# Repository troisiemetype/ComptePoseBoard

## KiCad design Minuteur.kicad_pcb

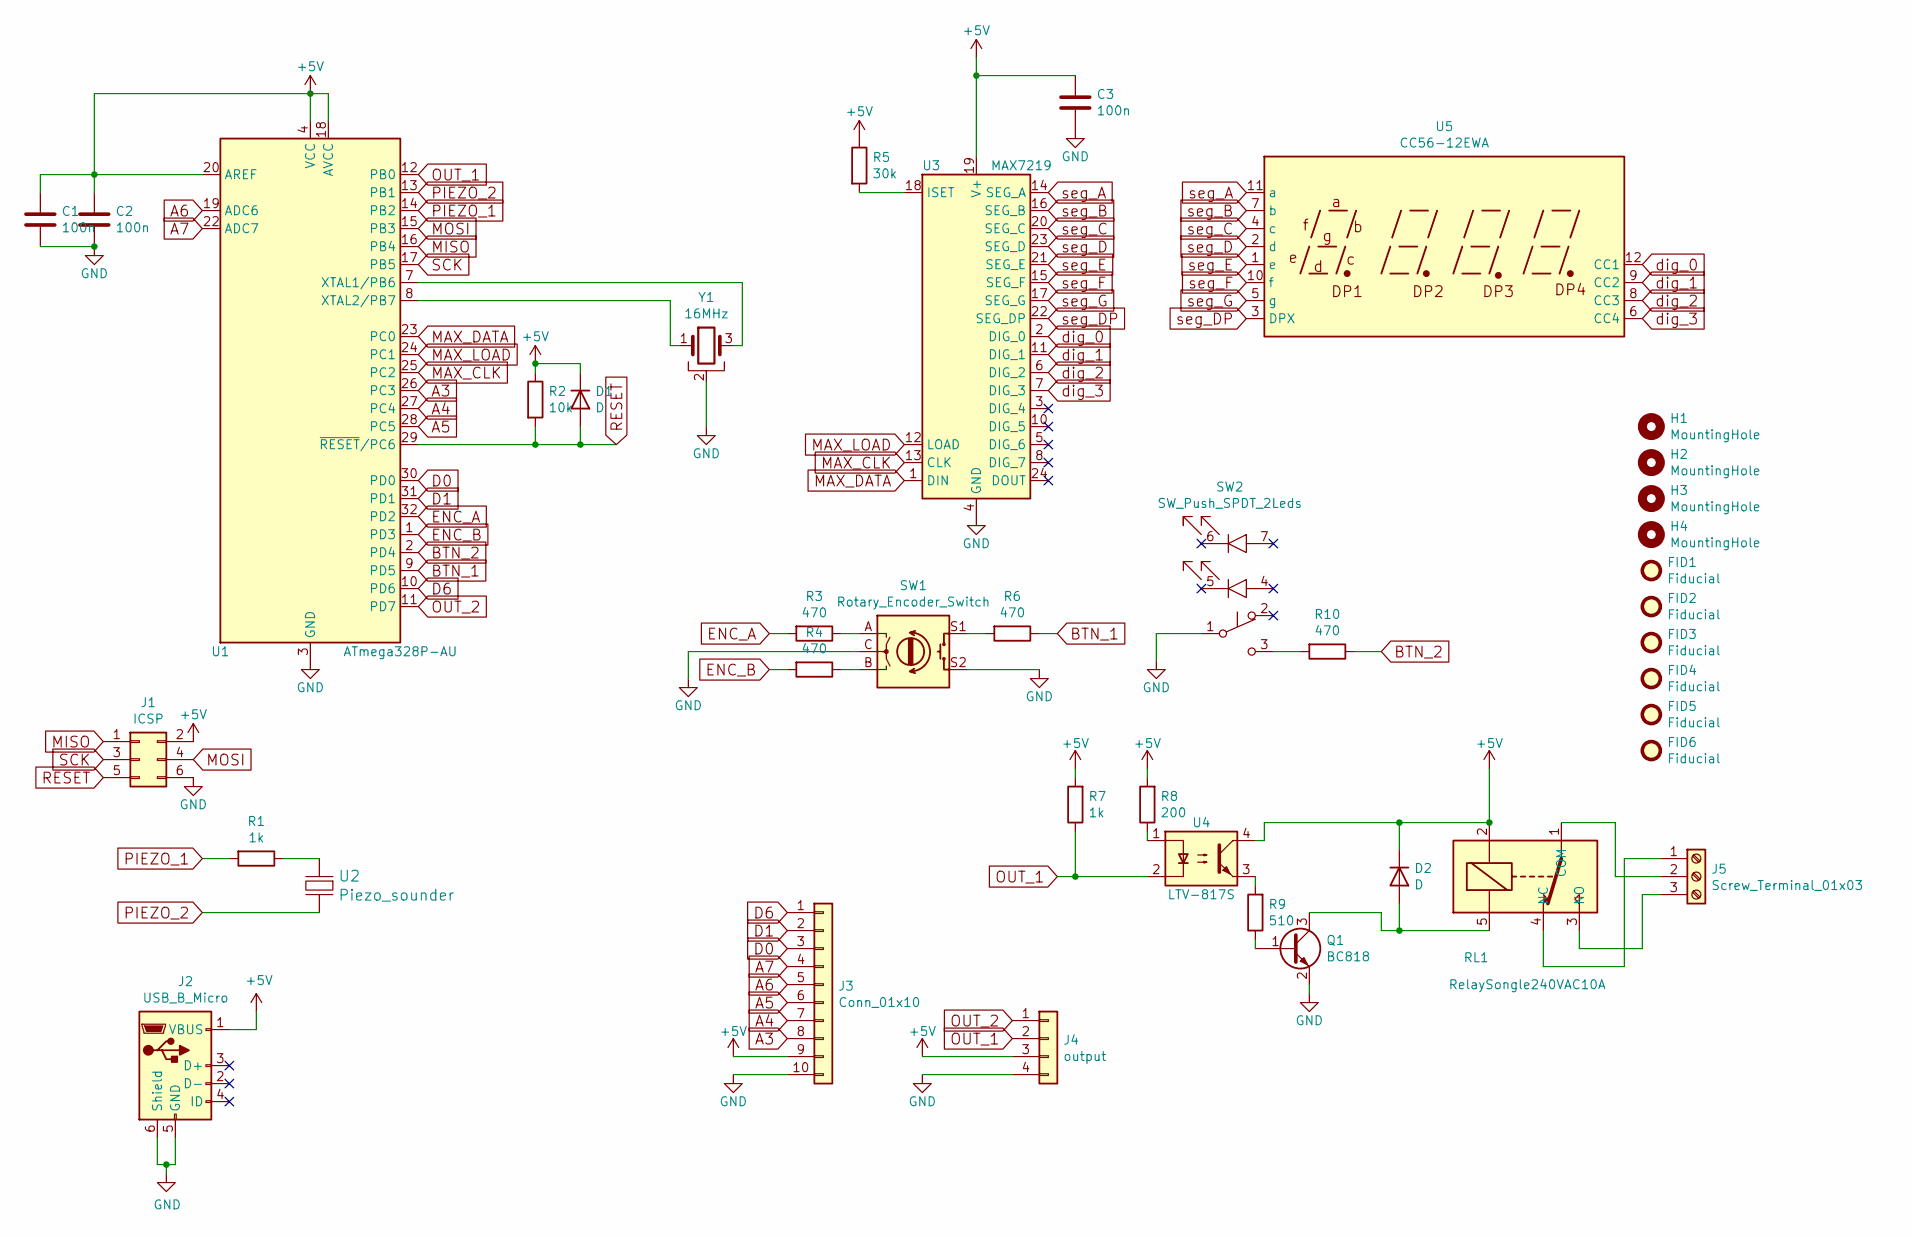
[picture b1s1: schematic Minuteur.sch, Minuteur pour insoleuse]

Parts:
C1, C2, C3: 100n; C_0805_2012Metric
D1, D2: D; D_SOD-123
FID1, FID2, FID3, FID4, FID5, FID6: Fiducial; Fiducial_0.75mm_Mask1.5mm
H1, H2, H3, H4: MountingHole; MountingHole_3.2mm_M3
J1: ICSP; PinHeader_2x03_P2.54mm_Vertical
J2: USB_B_Micro; USB_Micro-B_Amphenol_10118194_Horizontal
J3: Conn_01x10; PinHeader_1x10_P2.54mm_Vertical
J4: output; PinHeader_1x04_P2.54mm_Vertical
J5: Screw_Terminal_01x03; PhoenixContact_MSTBVA_2,5_3-G-5,08_1x03_P5.08mm_Vertical
Q1: BC818; SOT-23
R1, R7: 1k; R_0805_2012Metric
R2: 10k; R_0805_2012Metric
R3, R4, R6, R10: 470; R_0805_2012Metric
R5: 30k; R_0805_2012Metric
R8: 200; R_0805_2012Metric
R9: 510; R_0805_2012Metric
RL1: RelaySongle240VAC10A; Relay_SPDT_SANYOU_SRD_Series_Form_C
SW1: Rotary_Encoder_Switch; RotaryEncoder_Alps_EC12E-Switch_Vertical_H20mm_CircularMoun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
SW2: SW_Push_SPDT_2Leds; SP86-THT-PushButton
U1: ATmega328P-AU; TQFP-32_7x7mm_P0.8mm
U2: Piezo_sounder; Murata_PKMCS0909_xxxxx
U3: MAX7219; SOIC-24W_7.5x15.4mm_P1.27mm
U4: LTV-817S; SMDIP-4_W9.53mm
U5: CC56-12EWA; CA56-12EWA
Y1: 16MHz; Resonator_SMD_muRata_CSTxExxV-3Pin_3.0x1.1mm

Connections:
+5V: C1.1, C2.1, C3.1, D1.1 (K), D2.1 (K), J1.2, J2.1 (VBUS), J3.9, J4.3, R2.1, R5.1, R7.2, R8.2, RL1.2, U1.4 (VCC), U1.6 (VCC), U1.18 (AVCC), U1.20 (AREF), U3.19 (V+), U4.4; also elsewhere on the board
A3: J3.8, U1.26 (PC3); also elsewhere on the board
A4: J3.7, U1.27 (PC4); also elsewhere on the board
A5: J3.6, U1.28 (PC5); also elsewhere on the board
A6: J3.5, U1.19 (ADC6); also elsewhere on the board
A7: J3.4, U1.22 (ADC7); also elsewhere on the board
BTN_1: R6.1, U1.9 (PD5)
BTN_2: R10.1, U1.2 (PD4)
D0: J3.3, U1.30 (PD0); also elsewhere on the board
D1: J3.2, U1.31 (PD1); also elsewhere on the board
D6: J3.1, U1.10 (PD6); also elsewhere on the board
ENC_A: R3.2, U1.32 (PD2)
ENC_B: R4.2, U1.1 (PD3)
GND: C1.2, C2.2, C3.2, J1.6, J2.5 (GND), J2.6 (Shield), J3.10, J4.4, Q1.2 (E), SW1.C, SW1.S2, SW2.1 (B), U1.3 (GND), U1.5 (GND), U1.21 (GND), U3.4 (GND), U3.9 (GND), Y1.2; also elsewhere on the board
MAX_CLK: U1.25 (PC2), U3.13 (CLK)
MAX_DATA: U1.23 (PC0), U3.1 (DIN)
MAX_LOAD: U1.24 (PC1), U3.12 (LOAD)
MISO: J1.1, U1.16 (PB4); also elsewhere on the board
MOSI: J1.4, U1.15 (PB3); also elsewhere on the board
unnamed: D2.2 (A), Q1.3 (C), RL1.5
unnamed: J5.1, RL1.4 (NC)
unnamed: J5.2, RL1.1 (COM)
unnamed: J5.3, RL1.3 (NO)
unnamed: Q1.1 (B), R9.1
unnamed: R1.1, U2.1
unnamed: R3.1, SW1.A
unnamed: R4.1, SW1.B
unnamed: R5.2, U3.18 (ISET)
unnamed: R6.2, SW1.S1
unnamed: R8.1, U4.1
unnamed: R9.2, U4.3
unnamed: R10.2, SW2.3 (C)
unnamed: U1.7 (XTAL1/PB6), Y1.3
unnamed: U1.8 (XTAL2/PB7), Y1.1
OUT_1: J4.2, R7.1, U1.12 (PB0), U4.2; also elsewhere on the board
OUT_2: J4.1, U1.11 (PD7); also elsewhere on the board
PIEZO_1: R1.2, U1.14 (PB2)
PIEZO_2: U1.13 (PB1), U2.2
RESET: D1.2 (A), J1.5, R2.2, U1.29 (~RESET~/PC6); also elsewhere on the board
SCK: J1.3, U1.17 (PB5); also elsewhere on the board
dig_0: U3.2 (DIG_0), U5.12 (CC1)
dig_1: U3.11 (DIG_1), U5.9 (CC2)
dig_2: U3.6 (DIG_2), U5.8 (CC3)
dig_3: U3.7 (DIG_3), U5.6 (CC4)
seg_A: U3.14 (SEG_A), U5.11 (a)
seg_B: U3.16 (SEG_B), U5.7 (b)
seg_C: U3.20 (SEG_C), U5.4 (c)
seg_D: U3.23 (SEG_D), U5.2 (d)
seg_DP: U3.22 (SEG_DP), U5.3 (DPX)
seg_E: U3.21 (SEG_E), U5.1 (e)
seg_F: U3.15 (SEG_F), U5.10 (f)
seg_G: U3.17 (SEG_G), U5.5 (g)

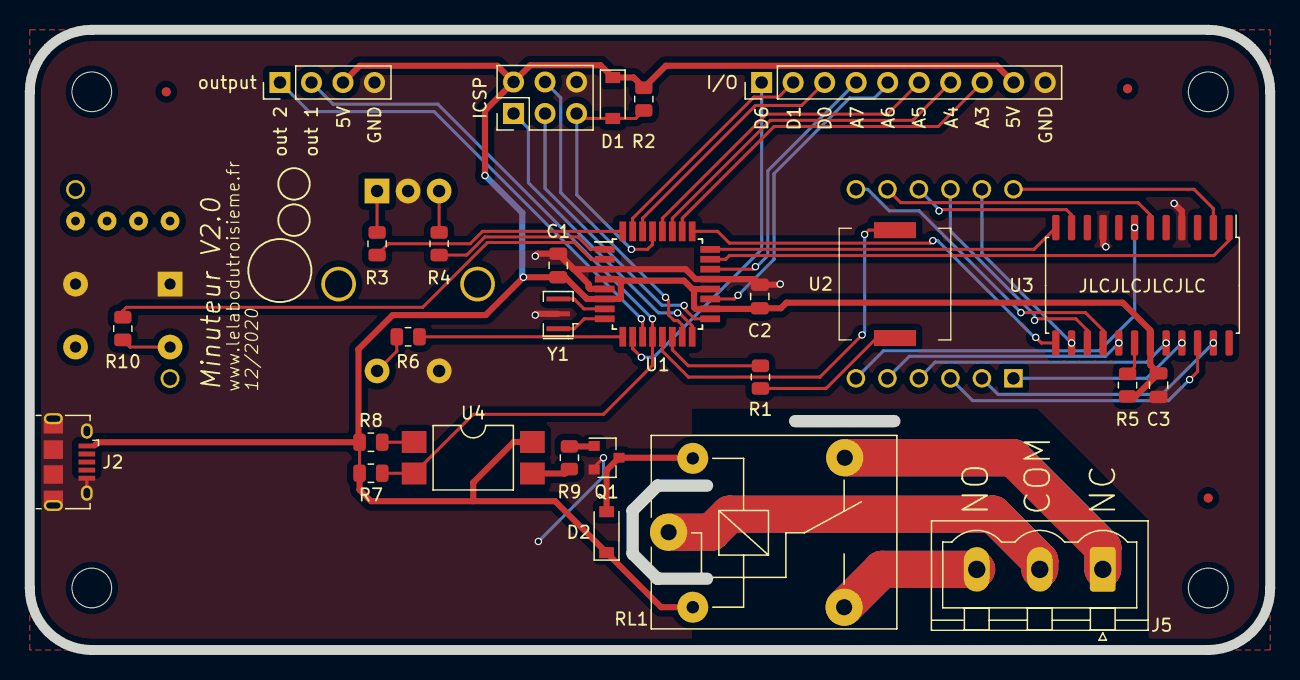
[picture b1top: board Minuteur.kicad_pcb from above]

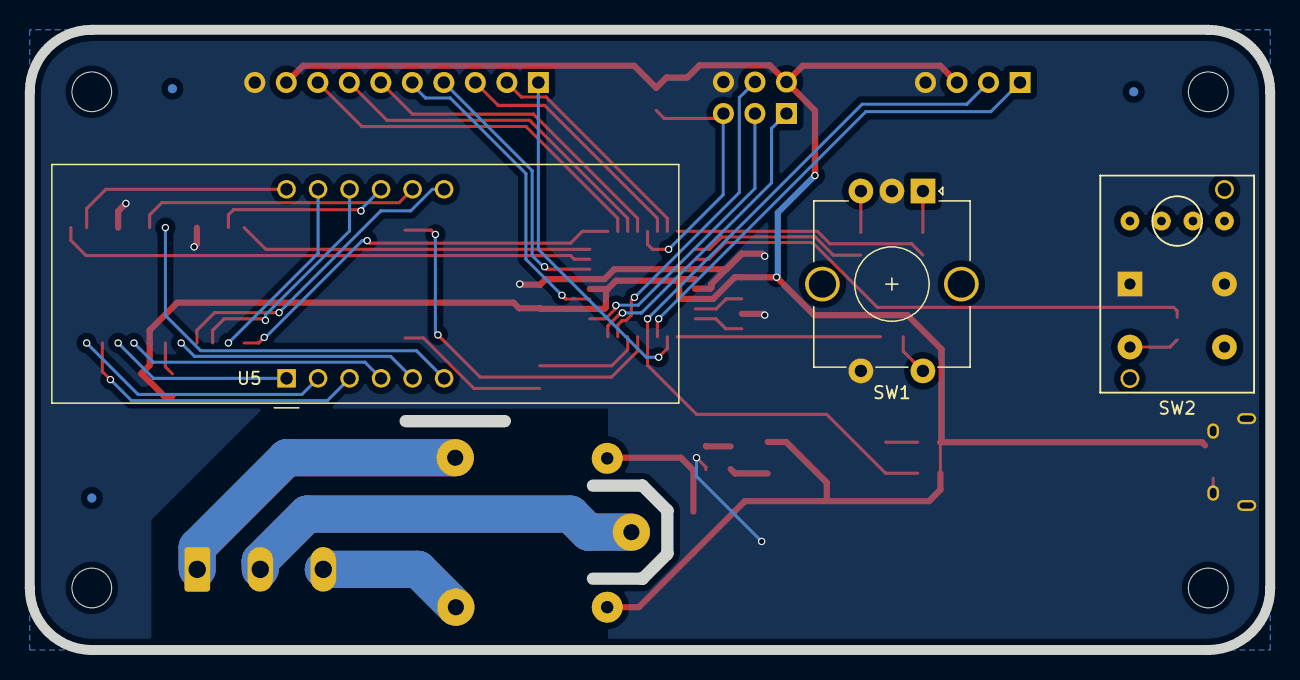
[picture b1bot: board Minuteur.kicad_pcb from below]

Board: 2 copper layers, 99.8 x 49.8 mm, 40 parts (6 on the bottom side), 52 nets.

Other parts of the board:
I/O: Conn_01x10; PinHeader_1x10_P2.54mm_Vertical
ICSP: ICSP; PinHeader_2x03_P2.54mm_Vertical
output: output; PinHeader_1x04_P2.54mm_Vertical

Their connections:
+5V: I/O.9, ICSP.2, output.3; also elsewhere on the board
A3: I/O.8; also elsewhere on the board
A4: I/O.7; also elsewhere on the board
A5: I/O.6; also elsewhere on the board
A6: I/O.5; also elsewhere on the board
A7: I/O.4; also elsewhere on the board
D0: I/O.3; also elsewhere on the board
D1: I/O.2; also elsewhere on the board
D6: I/O.1; also elsewhere on the board
GND: I/O.10, ICSP.6, output.4; also elsewhere on the board
MISO: ICSP.1; also elsewhere on the board
MOSI: ICSP.4; also elsewhere on the board
OUT_1: output.2; also elsewhere on the board
OUT_2: output.1; also elsewhere on the board
RESET: ICSP.5; also elsewhere on the board
SCK: ICSP.3; also elsewhere on the board

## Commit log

2017-06-08 Initial commit.
2017-06-08 v0.9 ready for fab.
2017-09-18 Ready for fab.
2017-10-20 Preparing v1 fab launch.
2017-10-20 Minuteur v1 ready for fab.
2020-06-23 Commit pre-v2.
2020-11-24 Commit last changes (probably Kicad wanting me to update footprints library) before switching to V2, with a new shaape for the board.
2020-12-01 General layout done.
2020-12-01 Routing done. Maybe need to move down extension connectors a little. Also need to replace the piezo connector by a SMD one.
2020-12-02 All routing done, DRC ok.
2020-12-03 Smaller version (100x50mm) routed. optocoupler changed. R-serie resistance for optocoupler changed to 200Ohm, so the optocoupler is in saturated region. Power lines have been changed from 0.25 to 0.5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
2020-12-03 AC version ready for fab.

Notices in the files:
Minuteur.sch:
distribué sous licence GNU GPL 3
